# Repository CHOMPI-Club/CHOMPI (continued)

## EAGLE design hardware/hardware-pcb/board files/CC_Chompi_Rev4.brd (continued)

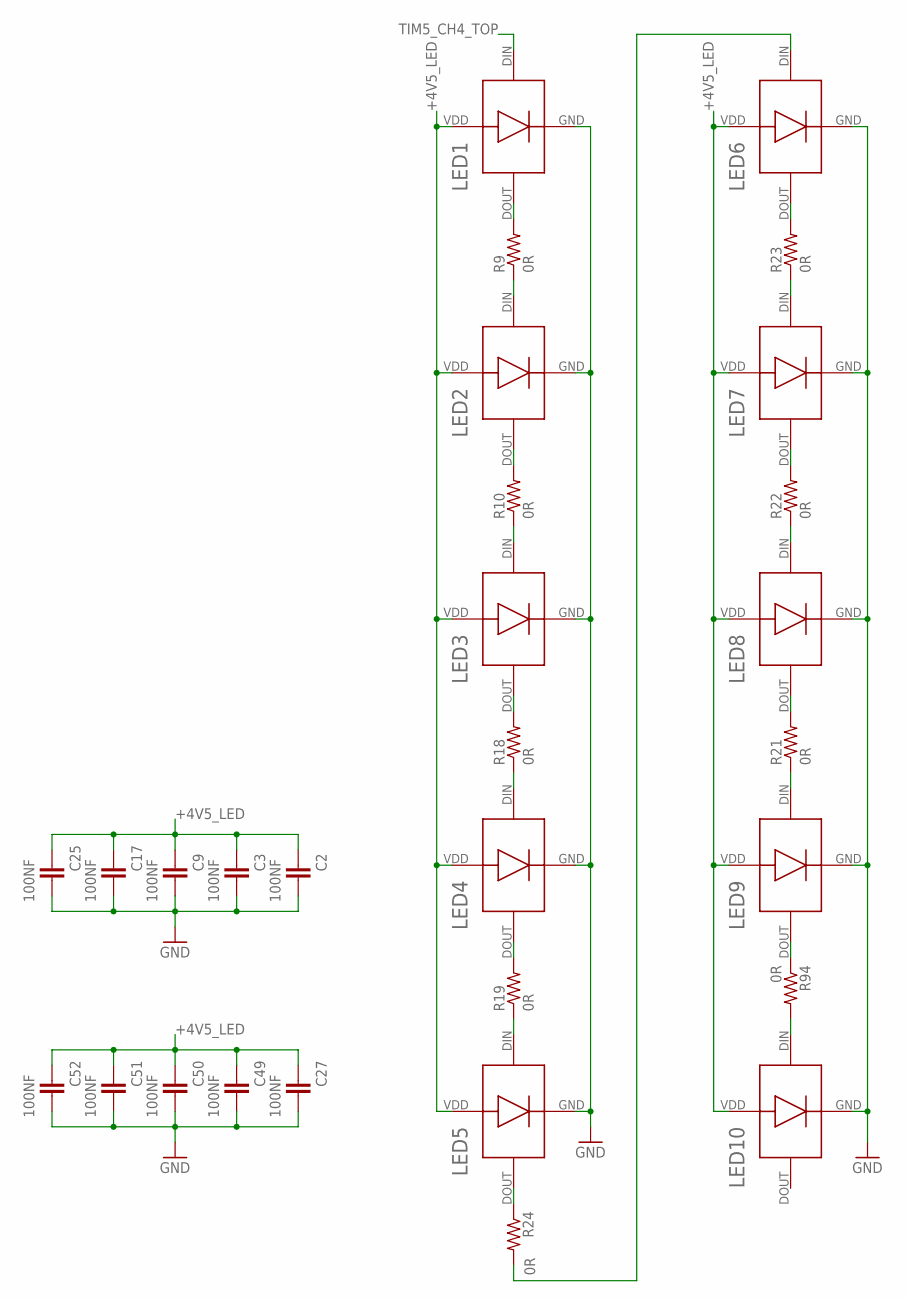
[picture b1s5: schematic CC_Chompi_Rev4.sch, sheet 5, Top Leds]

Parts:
C2, C3, C9, C17, C25, C27, C49, C50, C51, C52: 100NF; C0402
LED1, LED2, LED4, LED5, LED10: WS2812D-F8
LED3: DIGITAL_LEDWS2812D-F8-SPLIT; WS2812D-F8-SPLIT
LED6, LED7, LED8, LED9: DIGITAL_LEDWS2812D-F5; WS2812D-F5
R9, R10, R18, R19, R21, R22, R23, R24, R94: 0R; R0603

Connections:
+4V5_LED: C2.1, C3.1, C9.1, C17.1, C25.1, C27.1, C49.1, C50.1, C51.1, C52.1, LED1.VDD, LED2.VDD, LED3.VDD, LED4.VDD, LED5.VDD, LED6.VDD, LED7.VDD, LED8.VDD, LED9.VDD, LED10.VDD; also elsewhere on the board
GND: C2.2, C3.2, C9.2, C17.2, C25.2, C27.2, C49.2, C50.2, C51.2, C52.2, LED1.GND (VSS), LED2.GND (VSS), LED3.GND (VSS), LED4.GND (VSS), LED5.GND (VSS), LED6.GND (VSS), LED7.GND (VSS), LED8.GND (VSS), LED9.GND (VSS), LED10.GND (VSS); also elsewhere on the board
unnamed: LED9.DOUT (DO), R94.1
unnamed: LED10.DIN (DI), R94.2
unnamed: LED8.DOUT (DO), R21.2
unnamed: LED5.DOUT (DO), R24.1
unnamed: LED1.DOUT (DO), R9.2
unnamed: LED2.DIN (DI), R9.1
unnamed: LED2.DOUT (DO), R10.2
unnamed: LED3.DIN (DI), R10.1
unnamed: LED3.DOUT (DO), R18.2
unnamed: LED4.DIN (DI), R18.1
unnamed: LED4.DOUT (DO), R19.2
unnamed: LED5.DIN (DI), R19.1
unnamed: LED9.DIN (DI), R21.1
unnamed: LED7.DOUT (DO), R22.2
unnamed: LED8.DIN (DI), R22.1
unnamed: LED6.DOUT (DO), R23.2
unnamed: LED7.DIN (DI), R23.1
unnamed: LED6.DIN (DI), R24.2
TIM5_CH4_TOP: LED1.DIN (DI); also elsewhere on the board

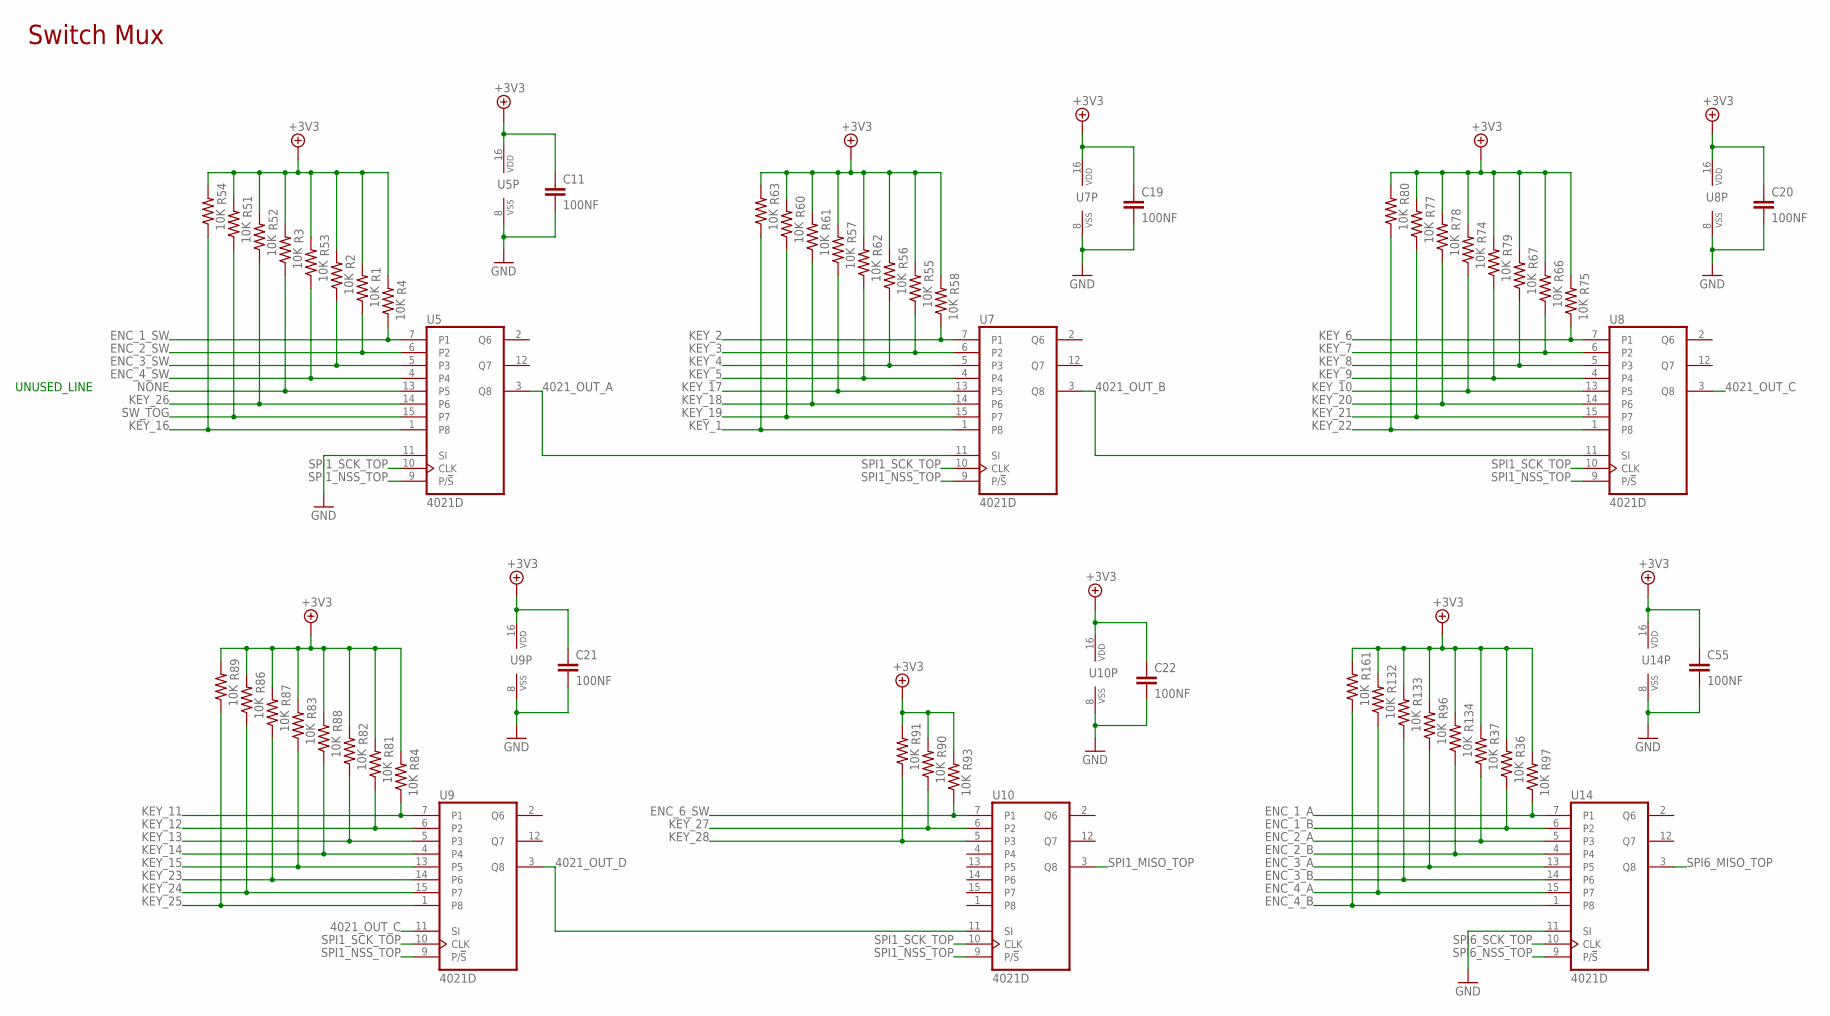
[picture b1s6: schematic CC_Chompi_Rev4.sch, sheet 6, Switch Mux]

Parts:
C11, C19, C20, C21, C22, C55: 100NF; C0402
R1, R2, R3, R4, R36, R37, R51, R52, R53, R54, R55, R56, R57, R58, R60, R61, R62, R63, R66, R67, R74, R75, R77, R78, R79, R80, R81, R82, R83, R84, R86, R87, R88, R89, R90, R91, R93, R96, R97, R132, R133, R134, R161: 10K; R0603
U5, U7, U8, U9, U10, U14: 4021D; SO-16

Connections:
4021_OUT_A: U5.3 (Q8), U7.11 (SI)
4021_OUT_B: U7.3 (Q8), U8.11 (SI)
4021_OUT_C: U8.3 (Q8), U9.11 (SI)
4021_OUT_D: U9.3 (Q8), U10.11 (SI)
+3V3: C11.1, C19.1, C20.1, C21.1, C22.1, C55.1, R1.2, R2.2, R3.2, R4.2, R36.2, R37.2, R51.2, R52.2, R53.2, R54.2, R55.2, R56.2, R57.2, R58.2, R60.2, R61.2, R62.2, R63.2, R66.2, R67.2, R74.2, R75.2, R77.2, R78.2, R79.2, R80.2, R81.2, R82.2, R83.2, R84.2, R86.2, R87.2, R88.2, R89.2, R90.2, R91.2, R93.2, R96.2, R97.2, R132.2, R133.2, R134.2, R161.2, U5.16 (VDD), U7.16 (VDD), U8.16 (VDD), U9.16 (VDD), U10.16 (VDD), U14.16 (VDD); also elsewhere on the board
ENC_1_A: R97.1, U14.7 (P1); also elsewhere on the board
ENC_1_B: R36.1, U14.6 (P2); also elsewhere on the board
ENC_1_SW: R4.1, U5.7 (P1); also elsewhere on the board
ENC_2_A: R37.1, U14.5 (P3); also elsewhere on the board
ENC_2_B: R134.1, U14.4; also elsewhere on the board
ENC_2_SW: R1.1, U5.6 (P2); also elsewhere on the board
ENC_3_A: R96.1, U14.13 (P5); also elsewhere on the board
ENC_3_B: R133.1, U14.14 (P6); also elsewhere on the board
ENC_3_SW: R2.1, U5.5 (P3); also elsewhere on the board
ENC_4_A: R132.1, U14.15 (P7); also elsewhere on the board
ENC_4_B: R161.1, U14.1 (P8); also elsewhere on the board
ENC_4_SW: R53.1, U5.4; also elsewhere on the board
ENC_6_SW: R93.1, U10.7 (P1); also elsewhere on the board
GND: C11.2, C19.2, C20.2, C21.2, C22.2, C55.2, U5.8 (VSS), U5.11 (SI), U7.8 (VSS), U8.8 (VSS), U9.8 (VSS), U10.8 (VSS), U14.8 (VSS), U14.11 (SI); also elsewhere on the board
KEY_1: R63.1, U7.1 (P8); also elsewhere on the board
KEY_2: R58.1, U7.7 (P1); also elsewhere on the board
KEY_3: R55.1, U7.6 (P2); also elsewhere on the board
KEY_4: R56.1, U7.5 (P3); also elsewhere on the board
KEY_5: R62.1, U7.4; also elsewhere on the board
KEY_6: R75.1, U8.7 (P1); also elsewhere on the board
KEY_7: R66.1, U8.6 (P2); also elsewhere on the board
KEY_8: R67.1, U8.5 (P3); also elsewhere on the board
KEY_9: R79.1, U8.4; also elsewhere on the board
KEY_10: R74.1, U8.13 (P5); also elsewhere on the board
KEY_11: R84.1, U9.7 (P1); also elsewhere on the board
KEY_12: R81.1, U9.6 (P2); also elsewhere on the board
KEY_13: R82.1, U9.5 (P3); also elsewhere on the board
KEY_14: R88.1, U9.4; also elsewhere on the board
KEY_15: R83.1, U9.13 (P5); also elsewhere on the board
KEY_16: R54.1, U5.1 (P8); also elsewhere on the board
KEY_17: R57.1, U7.13 (P5); also elsewhere on the board
KEY_18: R61.1, U7.14 (P6); also elsewhere on the board
KEY_19: R60.1, U7.15 (P7); also elsewhere on the board
KEY_20: R78.1, U8.14 (P6); also elsewhere on the board
KEY_21: R77.1, U8.15 (P7); also elsewhere on the board
KEY_22: R80.1, U8.1 (P8); also elsewhere on the board
KEY_23: R87.1, U9.14 (P6); also elsewhere on the board
KEY_24: R86.1, U9.15 (P7); also elsewhere on the board
KEY_25: R89.1, U9.1 (P8); also elsewhere on the board
KEY_26: R52.1, U5.14 (P6); also elsewhere on the board
KEY_27: R90.1, U10.6 (P2); also elsewhere on the board
KEY_28: R91.1, U10.5 (P3); also elsewhere on the board
NONE: R3.1, U5.13 (P5)
SPI1_MISO_TOP: U10.3 (Q8); also elsewhere on the board
SPI1_NSS_TOP: U5.9 (P/!S), U7.9 (P/!S), U8.9 (P/!S), U9.9 (P/!S), U10.9 (P/!S); also elsewhere on the board
SPI1_SCK_TOP: U5.10 (CLK), U7.10 (CLK), U8.10 (CLK), U9.10 (CLK), U10.10 (CLK); also elsewhere on the board
SPI6_MISO_TOP: U14.3 (Q8); also elsewhere on the board
SPI6_NSS_TOP: U14.9 (P/!S); also elsewhere on the board
SPI6_SCK_TOP: U14.10 (CLK); also elsewhere on the board
SW_TOG: R51.1, U5.15 (P7); also elsewhere on the board

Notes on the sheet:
Switch Mux
UNUSED_LINE

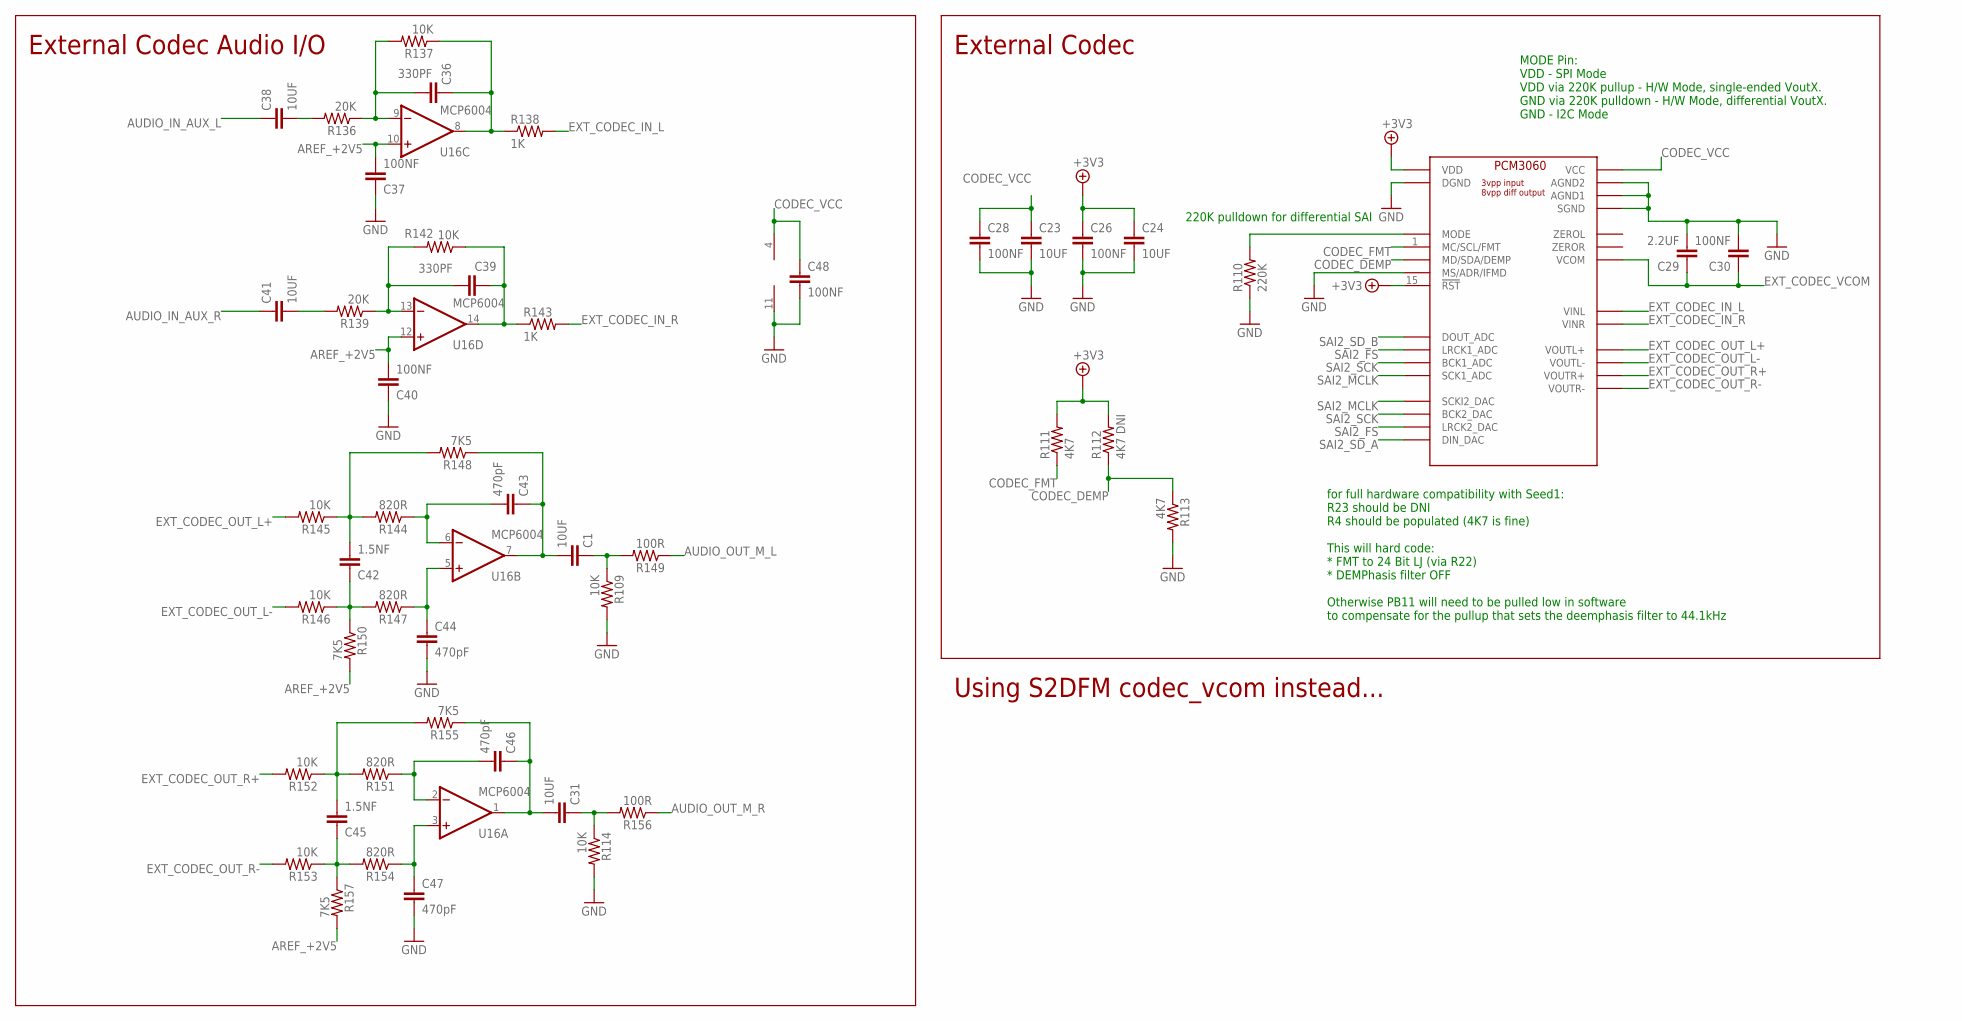
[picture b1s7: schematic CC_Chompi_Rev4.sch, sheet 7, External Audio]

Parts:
C1, C23, C24, C31, C38, C41: 10UF; C0805
C26, C28, C30, C37, C40, C48: 100NF; C0402
C29: 2.2UF; C0603
C36, C39: 330PF; C0603
C42, C45: 1.5NF; C0603
C43, C44, C46, C47: 470pF; C0603
R109, R114, R137, R142, R145, R146, R152, R153: 10K; R0603
R110: 220K; R0603
R111, R113: 4K7; R0603
R112: 4K7 DNI; R0603
R136, R139: 20K; R0603
R138, R143: 1K; R0402
R144, R147, R151, R154: 820R; R0603
R148, R150, R155, R157: 7K5; R0603
R149, R156: 100R; R0603
U12: PCM3060; TSSOP-28
U16: MCP6004; TSSOP-14

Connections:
+3V3: C24.1, C26.1, R111.2, R112.2, U12.7 (VDD), U12.15 (!RST); also elsewhere on the board
AREF_+2V5: C37.2, C40.2, R150.2, R157.2, U16.10 (+IN), U16.12 (+IN); also elsewhere on the board
AUDIO_IN_AMP_LEFT2: C38.2, R136.2
AUDIO_IN_AUX_L: C38.1; also elsewhere on the board
AUDIO_IN_AUX_R: C41.1; also elsewhere on the board
AUDIO_OUT_M_L: R149.1; also elsewhere on the board
AUDIO_OUT_M_R: R156.1; also elsewhere on the board
CODEC_DEMP: R112.1, R113.1, U12.2 (MD/SDA/DEMP)
CODEC_FMT: R111.1, U12.1 (MC/SCL/FMT)
CODEC_VCC: C23.1, C28.1, C48.1, U12.24 (VCC), U16.4 (V+); also elsewhere on the board
EXT_CODEC_IN_L: R138.2, U12.25 (VINL)
EXT_CODEC_IN_R: R143.2, U12.26 (VINR)
EXT_CODEC_OUT_L+: R145.2, U12.20 (VOUTL+)
EXT_CODEC_OUT_L-: R146.2, U12.19 (VOUTL-)
EXT_CODEC_OUT_R+: R152.2, U12.18 (VOUTR+)
EXT_CODEC_OUT_R-: R153.2, U12.17 (VOUTR-)
EXT_CODEC_VCOM: C29.1, C30.1, U12.21 (VCOM)
GND: C23.2, C24.2, C26.2, C28.2, C29.2, C30.2, C37.1, C40.1, C44.2, C47.2, C48.2, R109.2, R110.1, R113.2, R114.2, U12.8 (DGND), U12.16 (SGND), U12.22 (AGND2), U12.23 (AGND1), U12.27 (MS/ADR/IFMD), U16.11 (V-); also elsewhere on the board
HEADPHONE_IN_L2: C1.2, C43.1, R148.1, U16.7 (OUT)
HEADPHONE_IN_R2: C31.2, C46.1, R155.1, U16.1 (OUT)
unnamed: R110.2, U12.28 (MODE)
unnamed: C1.1, R109.1, R149.2
unnamed: C31.1, R114.1, R156.2
unnamed: C36.1, R137.1, R138.1, U16.8 (OUT)
unnamed: C36.2, R136.1, R137.2, U16.9 (-IN)
unnamed: C39.1, R142.1, R143.1, U16.14 (OUT)
unnamed: C39.2, R139.1, R142.2, U16.13 (-IN)
unnamed: C41.2, R139.2
unnamed: C43.2, R144.1, U16.6 (-IN)
unnamed: C44.1, R147.1, U16.5 (+IN)
unnamed: C42.1, R146.1, R147.2, R150.1
unnamed: C42.2, R144.2, R145.1, R148.2
unnamed: C46.2, R151.1, U16.2 (-IN)
unnamed: C47.1, R154.1, U16.3 (+IN)
unnamed: C45.1, R153.1, R154.2, R157.1
unnamed: C45.2, R151.2, R152.1, R155.2
SAI2_FS: U12.4 (LRCK1_ADC), U12.11 (LRCK2_DAC); also elsewhere on the board
SAI2_MCLK: U12.6 (SCK1_ADC), U12.9 (SCKI2_DAC); also elsewhere on the board
SAI2_SCK: U12.5 (BCK1_ADC), U12.10 (BCK2_DAC); also elsewhere on the board
SAI2_SD_A: U12.12 (DIN_DAC); also elsewhere on the board
SAI2_SD_B: U12.3 (DOUT_ADC); also elsewhere on the board

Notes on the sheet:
External Codec
MODE Pin: VDD - SPI Mode VDD via 220K pullup - H/W Mode, single-ended VoutX. GND via 220K pulldown - H/W Mode, differential VoutX. GND - I2C Mode
220K pulldown for differential SAI
for full hardware compatibility with Seed1: R23 should be DNI R4 should be populated (4K7 is fine) This will hard code: * FMT to 24 Bit LJ (via R22) * DEMPhasis filter OFF Otherwise PB11 will need to be pulled low in software to compensate for the pullup that sets the deemphasis filter to 44.1kHz
External Codec Audio I/O
Using S2DFM codec_vcom instead...

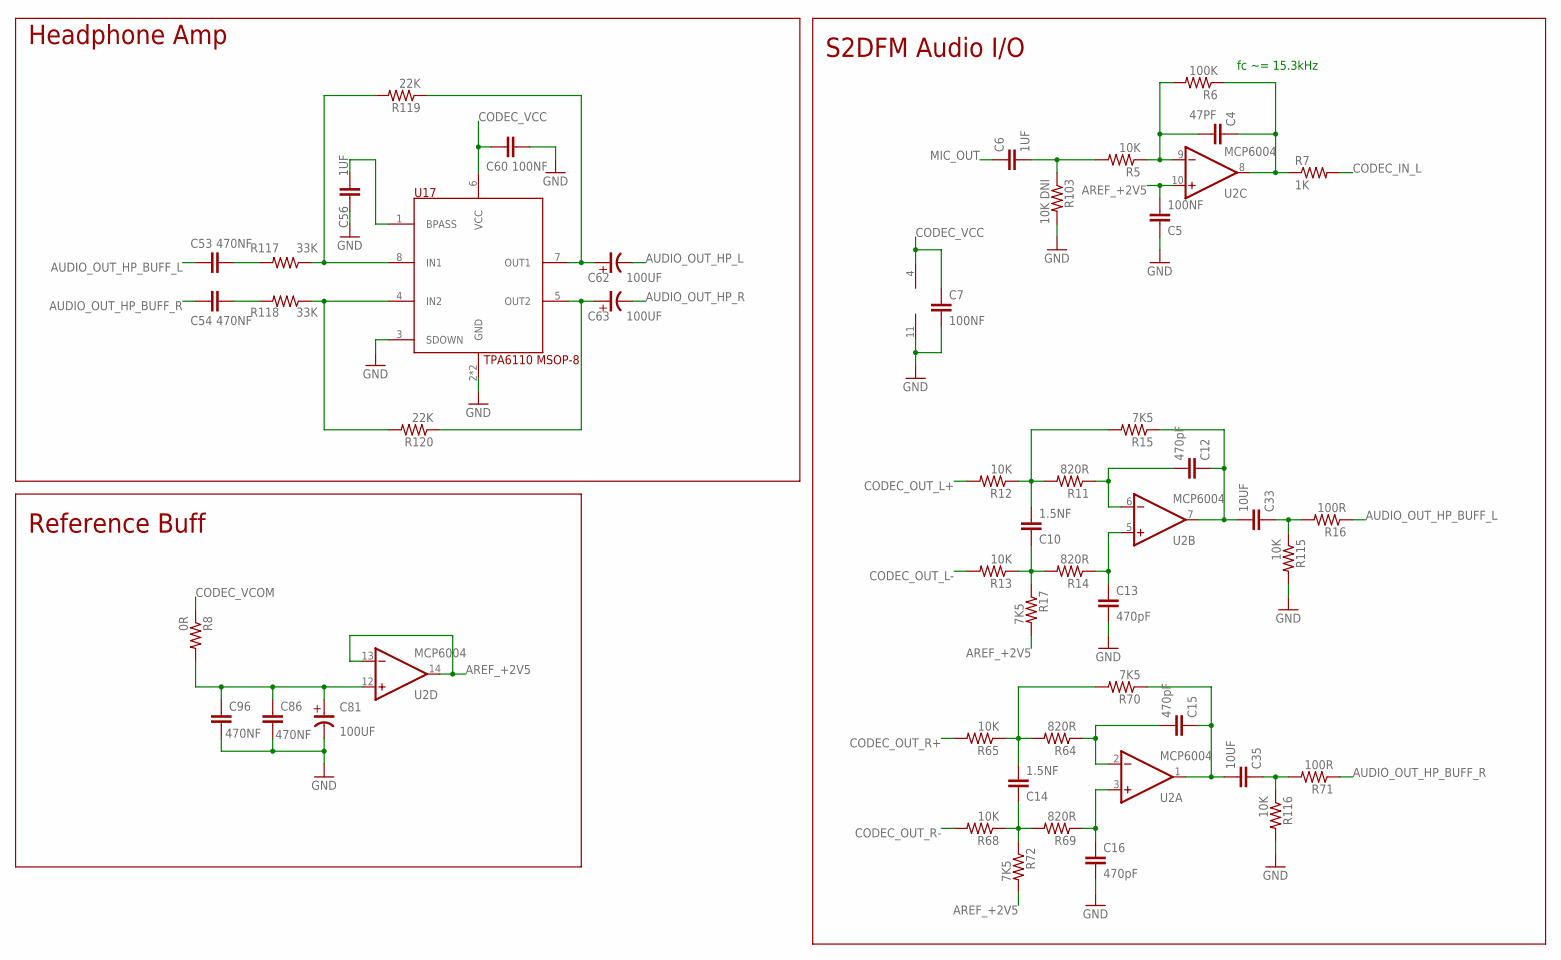
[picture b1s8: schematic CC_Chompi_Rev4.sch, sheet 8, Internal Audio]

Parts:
C4: 47PF; C0603
C5, C7, C60: 100NF; C0402
C6, C56: 1UF; C0603
C10, C14: 1.5NF; C0603
C12, C13, C15, C16: 470pF; C0603
C33, C35: 10UF; C0805
C53, C54, C86, C96: 470NF; C0603
C62, C63, C81: 100UF; PANASONIC_D
R5, R12, R13, R65, R68, R115, R116: 10K; R0603
R6: 100K; R0402
R7: 1K; R0402
R8: 0R; R0603
R11, R14, R64, R69: 820R; R0603
R15, R17, R70, R72: 7K5; R0603
R16, R71: 100R; R0603
R103: 10K DNI; R0603
R117, R118: 33K; R0603
R119, R120: 22K; R0603
U2: MCP6004; TSSOP-14
U17: TPA6110 MSOP-8; MSOP_8_PWRPAD

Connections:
AREF_+2V5: C5.2, R17.2, R72.2, U2.10 (+IN), U2.13 (-IN), U2.14 (OUT); also elsewhere on the board
AUDIO_IN_AMP_LEFT1: C6.2, R5.2, R103.1
AUDIO_OUT_HP_BUFF_L: C53.1, R16.1
AUDIO_OUT_HP_BUFF_R: C54.1, R71.1
AUDIO_OUT_HP_L: C62.- (NEG); also elsewhere on the board
AUDIO_OUT_HP_R: C63.- (NEG); also elsewhere on the board
CODEC_IN_L: R7.2; also elsewhere on the board
CODEC_OUT_L+: R12.2; also elsewhere on the board
CODEC_OUT_L-: R13.2; also elsewhere on the board
CODEC_OUT_R+: R65.2; also elsewhere on the board
CODEC_OUT_R-: R68.2; also elsewhere on the board
CODEC_VCC: C7.1, C60.2, U2.4 (V+), U17.6 (VCC); also elsewhere on the board
CODEC_VCOM: R8.1; also elsewhere on the board
GND: C5.1, C7.2, C13.2, C16.2, C56.1, C60.1, C81.- (NEG), C86.1, C96.1, R103.2, R115.2, R116.2, U2.11 (V-), U17.2 (GND), U17.3 (SDOWN), U17.9 (GND); also elsewhere on the board
HEADPHONE_IN_L1: C12.1, C33.2, R15.1, U2.7 (OUT)
HEADPHONE_IN_R1: C15.1, C35.2, R70.1, U2.1 (OUT)
MIC_OUT: C6.1; also elsewhere on the board
unnamed: C33.1, R16.2, R115.1
unnamed: C35.1, R71.2, R116.1
unnamed: C53.2, R117.2
unnamed: C54.2, R118.2
unnamed: C4.1, R6.1, R7.1, U2.8 (OUT)
unnamed: C4.2, R5.1, R6.2, U2.9 (-IN)
unnamed: C81.+ (POS), C86.2, C96.2, R8.2, U2.12 (+IN)
unnamed: C12.2, R11.1, U2.6 (-IN)
unnamed: C13.1, R14.1, U2.5 (+IN)
unnamed: R117.1, R119.2, U17.8 (IN1)
unnamed: R118.1, R120.2, U17.4 (IN2)
unnamed: C56.2, U17.1 (BPASS)
unnamed: C10.1, R13.1, R14.2, R17.1
unnamed: C62.+ (POS), R119.1, U17.7 (OUT1)
unnamed: C10.2, R11.2, R12.1, R15.2
unnamed: C15.2, R64.1, U2.2 (-IN)
unnamed: C16.1, R69.1, U2.3 (+IN)
unnamed: C14.1, R68.1, R69.2, R72.1
unnamed: C14.2, R64.2, R65.1, R70.2
unnamed: C63.+ (POS), R120.1, U17.5 (OUT2)

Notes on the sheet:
Headphone Amp
S2DFM Audio I/O
Reference Buff
fc ~= 15.3kHz

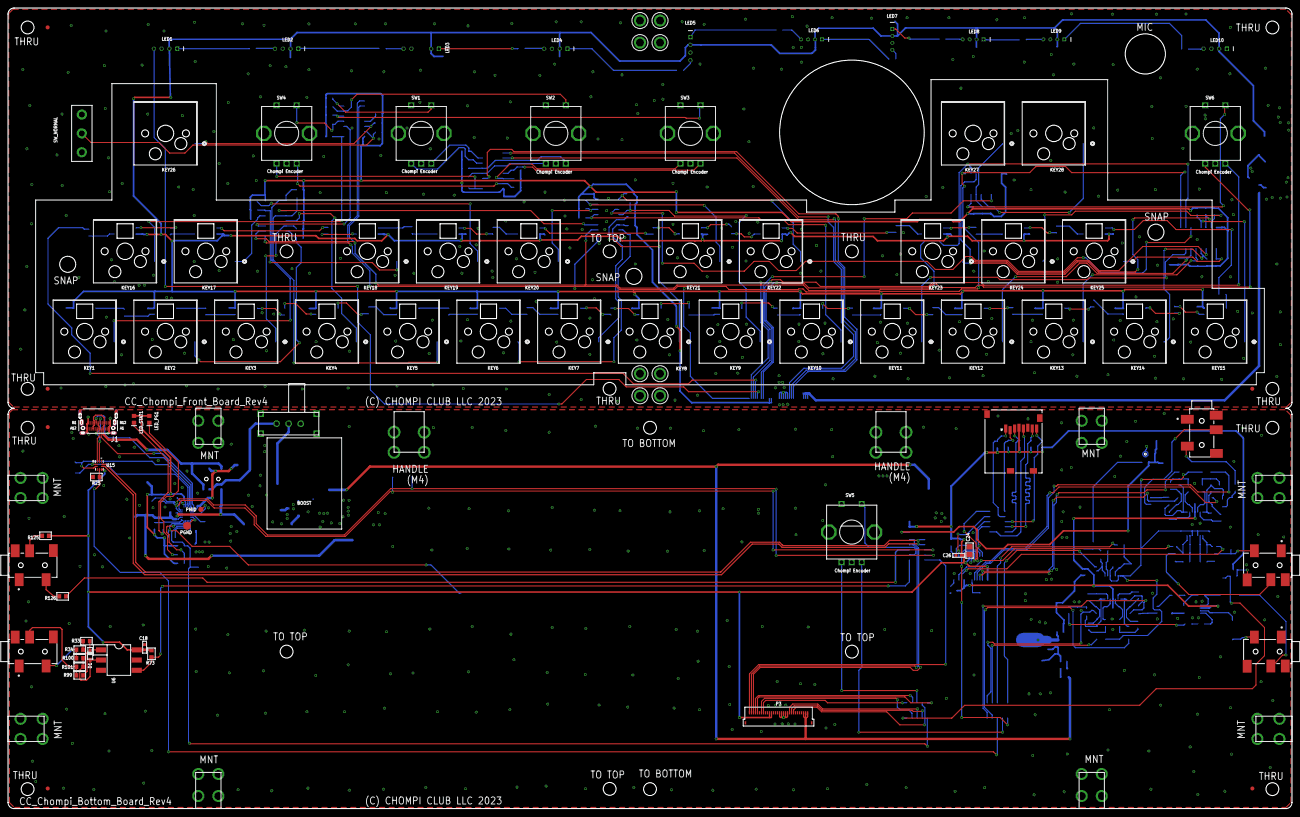
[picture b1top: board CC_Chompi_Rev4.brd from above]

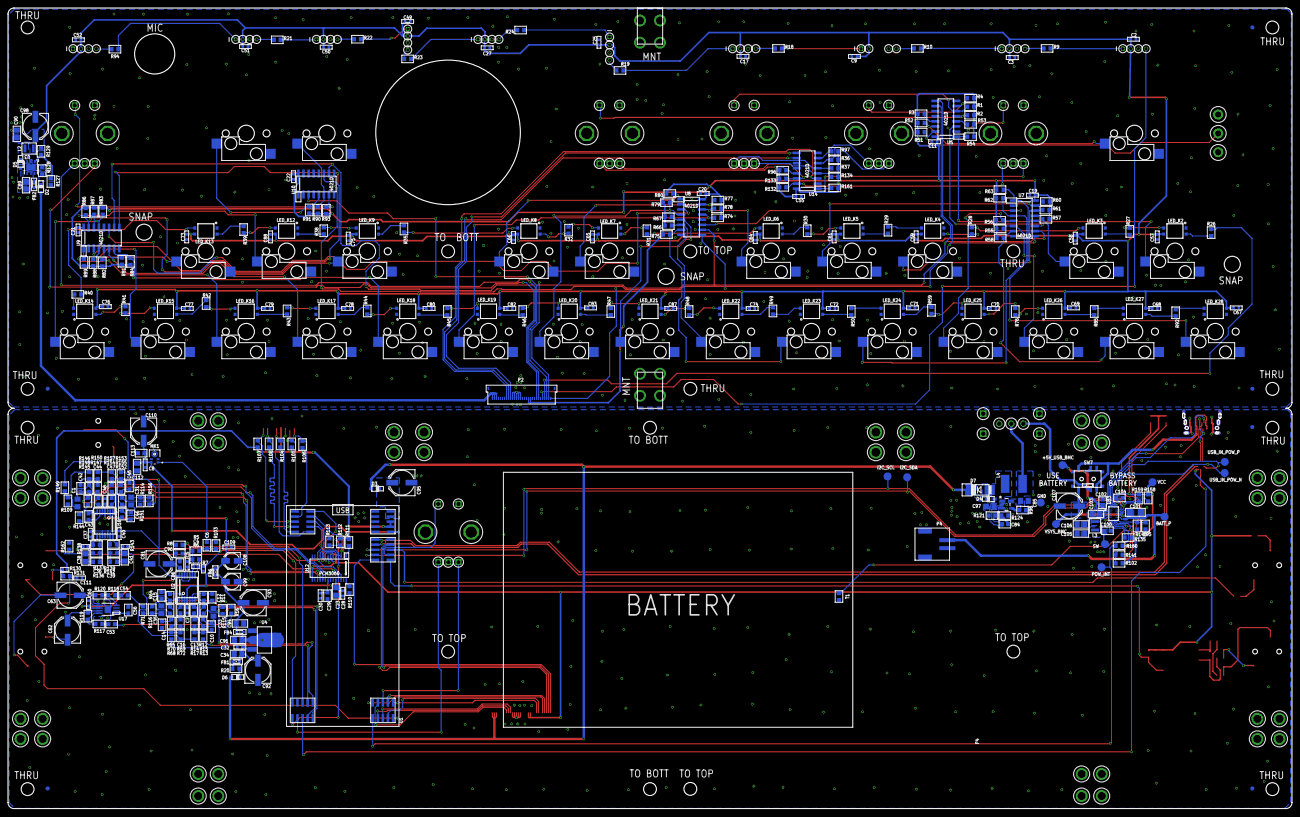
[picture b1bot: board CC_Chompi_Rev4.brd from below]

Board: 2 copper layers, 319.7 x 199.4 mm, 428 parts (367 on the bottom side), 273 nets.

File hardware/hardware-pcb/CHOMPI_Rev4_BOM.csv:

Qty,MPN,Value,Package,DNI,Designators
19,CL21A106KAYNNNF,10UF C0805,C0805,,C1 C23 C24 C31 C33 C34 C35 C38 C41 C85 C89 C90 C91 C94 C97 C103 C105 C106 C112
55,CC0402KPX5R8BB104,100NF C0402,C0402,,C2 C3 C5 C7 C8 C9 C11 C17 C18 C19 C20 C21 C22 C25 C26 C27 C28 C30 C32 C37 C40 C48 C49 C50 C51 C52 C55 C57 C58 C59 C60 C61 C64 C65 C66 C67 C68 C69 C70 C71 C72 C73 C74 C75 C76 C77 C78 C79 C80 C82 C83 C87 C88 C109 C111
1,0603N470K250CG,47PF C0603,C0603,,C4
4,CL10B105KA8NNNL,1UF C0603,C0603,,C6 C56 C102 C113
4,CC0603JRX7R9BB152,1.5NF C0603,C0603,,C10 C14 C42 C45
8,CC0603MRX7R9BB471,470PF C0603,C0603,,C12 C13 C15 C16 C43 C44 C46 C47
1,GRM188R61E225MA12J,2.2UF C0603,C0603,,C29
2,VJ0603Y331KXAPW1BC,330PF C0603,C0603,,C36 C39
4,CL10B474KA8NFNC,470NF C0603,C0603,,C53 C54 C86 C96
8,EMVE350ARA101MF80G,100UF PANASONIC D8,PANASONIC_D,,C62 C63 C81 C92 C93 C95 C98 C107
1,0603B221K250CG,220PF C0603,C0603,,C84
2,EEE-FK1E100R,10UF PANASONIC B,PANASONIC_B,,C99 C108
1,AC0603JRX7R9BB223,22NF C0603,C0603,,C100
1,1206X226K250CG,22UF C1206,C1206,,C101
1,GRM188R61E475KE11D,4.7UF C0603,C0603,,C104
6,NSR1020MW2T3G,NSR1020MW2T3G,SOD-323F,,D1 D2 D3 D4 D5 D6
4,BBPY00160808601Y00,FB R0603,WUERTH-ELEKTRONIK_0603,,FB1 FB2 FB4 FB6
2,GENERIC,M4 Screw Terminal,M4_SCREW_TERMINAL,,HANDLE_1 HANDLE_2
1,USB-C31-S-RA-CS2-SMT-BK-T/R,USB C 24 Pin Horizontal ADM,ADAM_USB-C31-S-RA-CS2-SMT-BK-T/R,,J1
5,PJ-327A-5P,SMT-JACK-S-H-3.5,CUI_SJ2-35863B1-SMT-TR,,J_AUDIO_IN J_AUDIO_OUT J_HP_OUT J_MIDI_IN J_MIDI_OUT
28,CPG151101S11-16,Kailh Cherry MX Socket,CPG151101S11,,KEY1 KEY2 KEY3 KEY4 KEY5 KEY6 KEY7 KEY8 KEY9 KEY10 KEY11 KEY12 KEY13 KEY14 KEY15 KEY16 KEY17 KEY18 KEY19 KEY20 KEY21 KEY22 KEY23 KEY24 KEY25 KEY26 KEY27 KEY28
2,AIML-1008HC-3R3M-T,3.3UH 1008 Inductor,I1008,,L2 L3
1,VLS5045EX-6R8M,6.8UH 5x5 INDUCTOR,MPL-SE6040,,L4
5,WS2812D-F8,8mm RGB PTH Digital LED,WS2812D-F8,,LED1 LED2 LED4 LED5 LED10
1,WS2812D-F8,8mm RGB PTH Digital LED,WS2812D-F8-SPLIT,,LED3
4,WS2812D-F5,5mm RGB PTH Digital LED,WS2812D-F5,,LED6 LED7 LED8 LED9
25,IN-PI32TAR5R5G5B-8113,Digital LED Reverse Mount,IN-PI32TAR,,LED_K2 LED_K3 LED_K4 LED_K5 LED_K6 LED_K7 LED_K8 LED_K9 LED_K12 LED_K13 LED_K14 LED_K15 LED_K16 LED_K17 LED_K18 LED_K19 LED_K20 LED_K21 LED_K22 LED_K23 LED_K24 LED_K25 LED_K26 LED_K27 LED_K28
2,APT1608SURCK,RED LED R0603,DIODE_0603,,LED_PG1 LED_STAT1
1,MP23ABS1TR,MP23ABS1TR,MIC_MP23ABS1TR,,MK1
2,FH34SRJ-30S-0-5SH-50,ZIF 30 Pin .5mm,FH34SRJ-30S-0-5SH-50,,P2 P3
1,S2B-PH-SM4-TB(LF)(SN),S2B-PH-SM4-TB Header,S2B-PH-SM4-TB(LF)(SN),,P4
1,MEM2061-01-188-00-A,SMT MICRO SD HORIZONTAL MEM20161,MEM2061-01-188-00-A_GCT,,P5
63,RC0603FR-1310KL,10K R0603,R0603,,R1 R2 R3 R4 R5 R12 R13 R36 R37 R51 R52 R53 R54 R55 R56 R57 R58 R60 R61 R62 R63 R65 R66 R67 R68 R74 R75 R77 R78 R79 R80 R81 R82 R83 R84 R86 R87 R88 R89 R90 R91 R93 R96 R97 R109 R114 R115 R116 R124 R132 R133 R134 R135 R137 R140 R141 R142 R145 R146 R152 R153 R161 R162
2,RC0402FR-13100KL,100K R0402,R0402,,R6 R130
3,RC0402FR-131KL,1K R0402,R0402,,R7 R138 R143
37,AC0603FR-070RL,0R R0603,R0603,,R8 R9 R10 R18 R19 R21 R22 R23 R24 R26 R27 R28 R29 R30 R31 R32 R35 R38 R39 R40 R41 R42 R43 R44 R45 R46 R47 R48 R49 R50 R59 R76 R85 R92 R94 R99 R100
8,RC0603FR-07820RL,820R R0603,R0603,,R11 R14 R64 R69 R144 R147 R151 R154
8,RC0603FR-107K5L,7K5 R0603,R0603,,R15 R17 R70 R72 R148 R150 R155 R157
4,RC0603FR-13100RL,100R R0603,R0603,,R16 R71 R149 R156
2,CR16-10R0-FY,10R R0603,R0603,,R20 R126
7,RC0603FR-134K7L,4K7 R0603,R0603,,R25 R111 R113 R128 R158 R159 R160
1,RC0603FR-07220RL,220R R0603,R0603,,R33
1,CRCW0603270RFKEAC,270R R0603,R0603,,R73
1,RC0603FR-131ML,1M R0603,R0603,,R98
6,RC0603FR-0747KL,47K R0603,R0603,,R104 R105 R106 R107 R108 R127
1,RC0603FR-07220KL,220K R0603,R0603,,R110
2,RC0603FR-1333KL,33K R0603,R0603,,R117 R118
2,RC0603FR-0722KL,22K R0603,R0603,,R119 R120
1,CR0603-FX-6652ELF,66K5 R0603,R0603,,R121
1,RC0603FR-0733RL,33R R0603,R0603,,R125
3,CR0603-FX-2002ELF,20K R0603,R0603,,R129 R136 R139
1,CR16-4992-FY,49K9 R0603,R0603,,R131
1,SK-12F17-G7,Right Angle Tactile Switch ON ON,SK-12F17-G7,,S1
8,T34069,M3 PTH Screw Terminal T34069,T34069_OLD,,SCREW_1 SCREW_2 SCREW_3 SCREW_4 SCREW_5 SCREW_7 SCREW_9 SCREW_10
1,T34069,M3 PTH Screw Terminal T34069,T34069_OLD_ADJ2,,SCREW_6
1,T34069,M3 PTH Screw Terminal T34069,T34069_OLD_ADJ1,,SCREW_8
6,EC12MSDV7BF-D-20F-24-19WE,CHOMPI Encoder,PEC11_SILK,,SW1 SW2 SW3 SW4 SW5 SW6
1,MSS6-V-T/R,MSS6-V-T/R,MSS6-V-T/R,,SW7
1,SS-12D10L9,Vertical Slide Switch ON ON,ES_100SP1T6B11M2QEH_SMALL,,SW_NORMAL
1,TX04F103F3380ER,10K NTC THERMISTOR 0603,R0603,,T1
1,ES_Daisy_Seed2_DFM_65MB,ES_Daisy_Seed2_DFM_65MB,ES_DAISY_SEED2_DFM_REV1,,U1
2,MCP6004T-I/ST,MCP6004 TSSOP-14,TSSOP-14,,U2 U16
1,ST1S03PUR,ST1S03 DFN6D,DFN06_3X3_STM,,U3
1,LD1117S50CTR,LD1117-5V,SOT223,,U4
6,CD4021BM96,CD4021 SO-16,SO-16,,U5 U7 U8 U9 U10 U14
1,H11L1SR2M,OPTO ISOLATOR,DIL06_GULLWING,,U6
1,LMR62421XMFX/NOPB,LMR62421 SOT-23-5,MF05A,,U11
1,PCM3060PWR,PCM3060 TSSOP-28,TSSOP-28,,U12
1,MP2722GRH-0000-Z,MP2722 Buck Charger,MP2722,,U13
1,USB3740B-AI9-TR,USB3740B QFN-10,QFN10_1P6X2P1MC_MCH,,U15
1,TPA6110A2DGNR,TPA6110 MSOP-8,MSOP_8_PWRPAD,,U17
1,EMVE350ARA101MF80G,100UF PANASONIC D8,PANASONIC_D,DNI,C110
1,B220A-13-F,B220A-13-F SMA,SMADIODE,DNI,D7
2,AC0603FR-070RL,0R R0603,R0603,DNI,R34 R101
3,RC0603FR-1310KL,10K R0603,R0603,DNI,R95 R102 R103
1,RC0603FR-134K7L,4K7 R0603,R0603,DNI,R112
